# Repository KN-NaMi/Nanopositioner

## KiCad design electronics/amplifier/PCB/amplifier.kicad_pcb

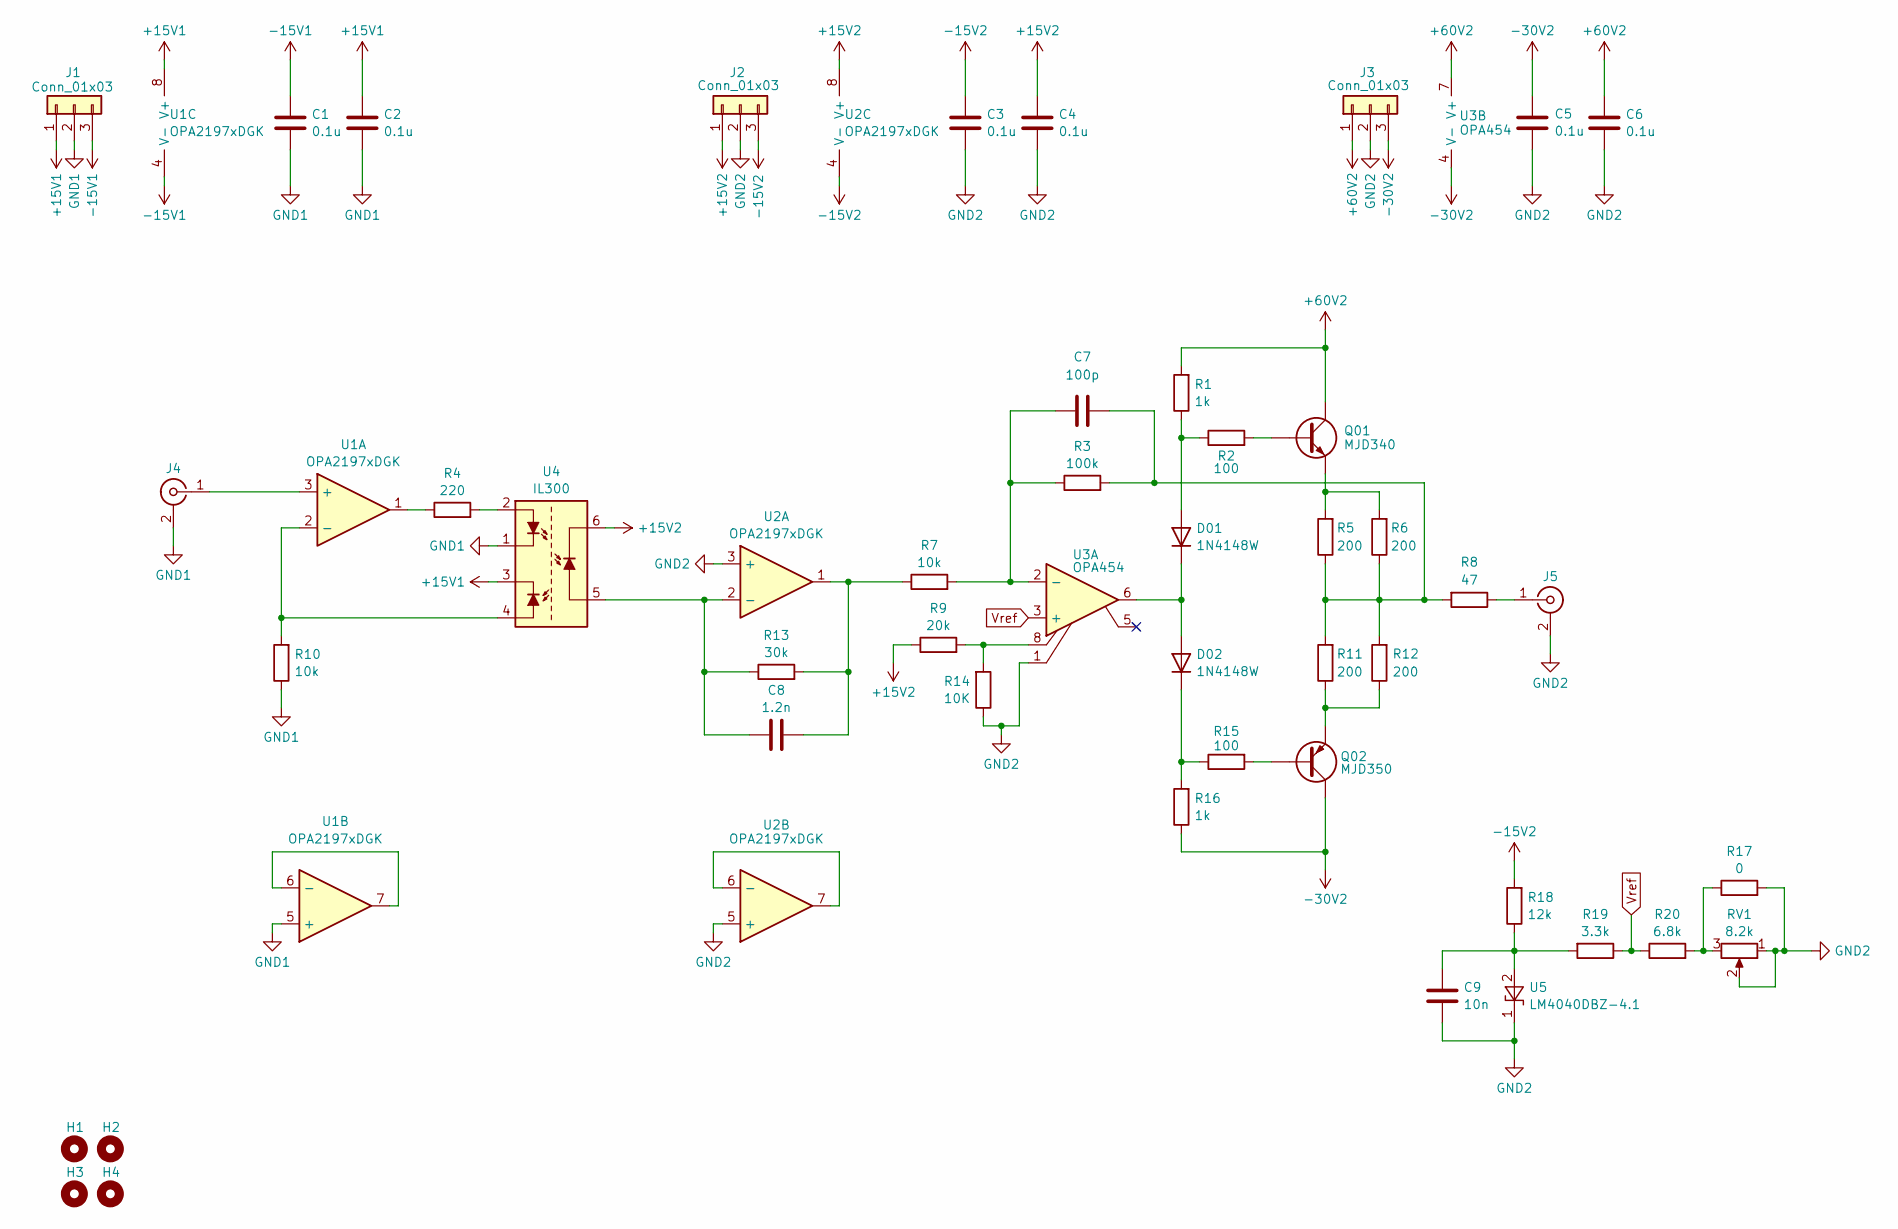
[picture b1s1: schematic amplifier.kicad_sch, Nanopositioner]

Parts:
C1, C2, C3, C4, C5: 0.1u; R_0603_1608Metric; Digikey 399-C0603C104K5RACTUCT-ND
C6: 0.1u; R_0603_1608Metric; Digikey 490-3285-1-ND
C7: 100p; C_0603_1608Metric; Digikey 3372-0603B101K101SDTR-ND
C8: 1.2n; C_0603_1608Metric; Digikey 490-1453-1-ND
C9: 10n; C_0603_1608Metric; Digikey 399-C0603C103K5RACTUCT-ND
D01, D02: 1N4148W; D_SOD-123; Digikey 1655-1N4148WCT-ND
H1, H2, H3, H4: MountingHole; MountingHole_3.2mm_M3_DIN965
J1, J2, J3: Conn_01x03; TerminalBlock_Phoenix_PT-1,5-3-5.0-H_1x03_P5.00mm_Horizontal; Digikey 732-10956-ND
J4, J5: Conn_Coaxial; SMA_Amphenol_132134_Vertical; Digikey 2073-RFPC-SMA28-F-ND
Q01: MJD340; TO-252-3_TabPin4; Digikey MJD340T4GOSCT-ND
Q02: MJD350; TO-252-3_TabPin4; Digikey MJD350T4GOSCT-ND
R1, R16: 1k; R_0603_1608Metric; Digikey 541-2788-1-ND
R2, R15: 100; R_0603_1608Metric; Digikey 541-2786-1-ND
R3: 100k; R_0805_2012Metric; Digikey 541-2850-1-ND
R4: 220; R_0603_1608Metric; Digikey 541-10437-1-ND
R5, R6, R11, R12: 200; R_2512_6332Metric; Digikey A116015CT-ND
R7, R10: 10k; R_0603_1608Metric; Digikey 541-2795-1-ND
R8: 47; R_2512_6332Metric; Digikey 118-CHP2512AFX-47R0ELFCT-ND
R9: 20k; R_0603_1608Metric; Digikey 541-2797-1-ND
R13: 30k; R_0603_1608Metric; Digikey 541-10453-1-ND
R14: 10K; R_0603_1608Metric; Digikey 541-2795-1-ND
R17: 0; R_0603_1608Metric
R18: 12k; R_0603_1608Metric; Digikey 541-10428-1-ND
R19: 3.3k; R_0603_1608Metric; Digikey 541-10464-1-ND
R20: 6.8k; R_0603_1608Metric; Digikey 541-10489-1-ND
RV1: 8.2k; Potentiometer_Vishay_T93YA_Vertical; Digikey 716-T63YA802KT20-ND
U1, U2: OPA2197xDGK; VSSOP-8_3x3mm_P0.65mm; Digikey 296-47349-1-ND
U3: OPA454; DDA0008J; Digikey 296-41370-1-ND
U4: IL300; SMDIP-8_W9.53mm_Clearance8mm; Digikey IL300-DEFG-X007-ND
U5: LM4040DBZ-4.1; SOT-23; Digikey LM4040AIM3-4.1/NOPBCT-ND

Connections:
+15V1: C2.1, J1.1, U1.8 (V+), U4.3
+15V2: C4.1, J2.1, R9.1, U2.8 (V+), U4.6
+60V2: C6.1, J3.1, Q01.C, R1.2, U3.7 (V+)
-15V1: C1.1, J1.3, U1.4 (V-)
-15V2: C3.1, J2.3, R18.2, U2.4 (V-)
-30V2: C5.1, J3.3, Q02.C, R16.1, U3.4 (V-)
GND1: C1.2, C2.2, J1.2, J4.2 (Ext), R10.1, U1.5 (+), U4.1
GND2: C3.2, C4.2, C5.2, C6.2, C9.1, J2.2, J3.2, J5.2 (Ext), R14.1, R17.2, RV1.1, RV1.2, U2.3 (+), U2.5 (+), U3.1, U5.1 (K)
unnamed: C7.2, R3.2, R5.1, R6.1, R8.2, R11.2, R12.2
unnamed: C8.2, R7.1, R13.2, U2.1
unnamed: D01.2 (A), R1.1, R2.1
unnamed: D01.1 (K), D02.2 (A), U3.6
unnamed: D02.1 (K), R15.1, R16.2
unnamed: J4.1 (In), U1.3 (+)
unnamed: J5.1 (In), R8.1
unnamed: Q01.B, R2.2
unnamed: Q01.E, R5.2, R6.2
unnamed: Q02.B, R15.2
unnamed: Q02.E, R11.1, R12.1
unnamed: R4.1, U1.1
unnamed: R4.2, U4.2
unnamed: R9.2, R14.2, U3.8
unnamed: R17.1, R20.2, RV1.3
unnamed: R10.2, U1.2 (-), U4.4
unnamed: U1.6 (-), U1.7
unnamed: C8.1, R13.1, U2.2 (-), U4.5
unnamed: U2.6 (-), U2.7
unnamed: C7.1, R3.1, R7.2, U3.2 (-)
unnamed: C9.2, R18.1, R19.2, U5.2 (A)
Vref: R19.1, R20.1, U3.3 (+)

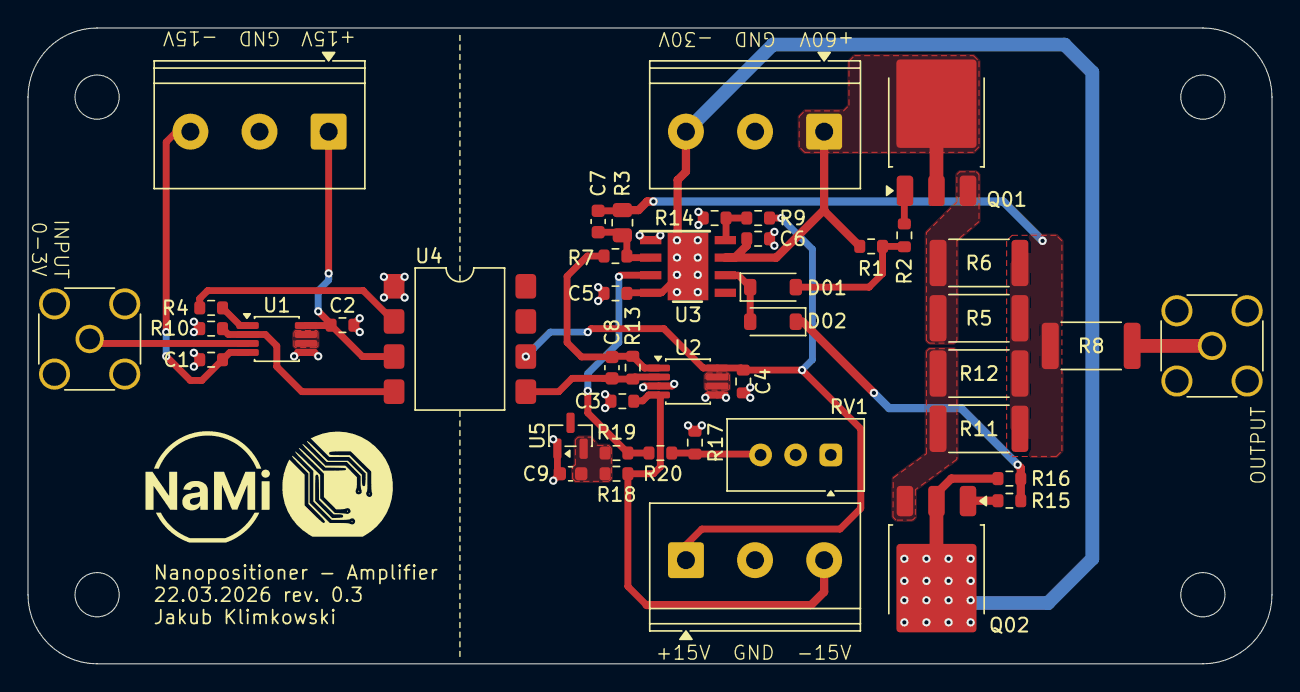
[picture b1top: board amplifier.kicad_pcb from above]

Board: 2 copper layers, 90.0 x 46.0 mm, 48 parts (0 on the bottom side), 30 nets.

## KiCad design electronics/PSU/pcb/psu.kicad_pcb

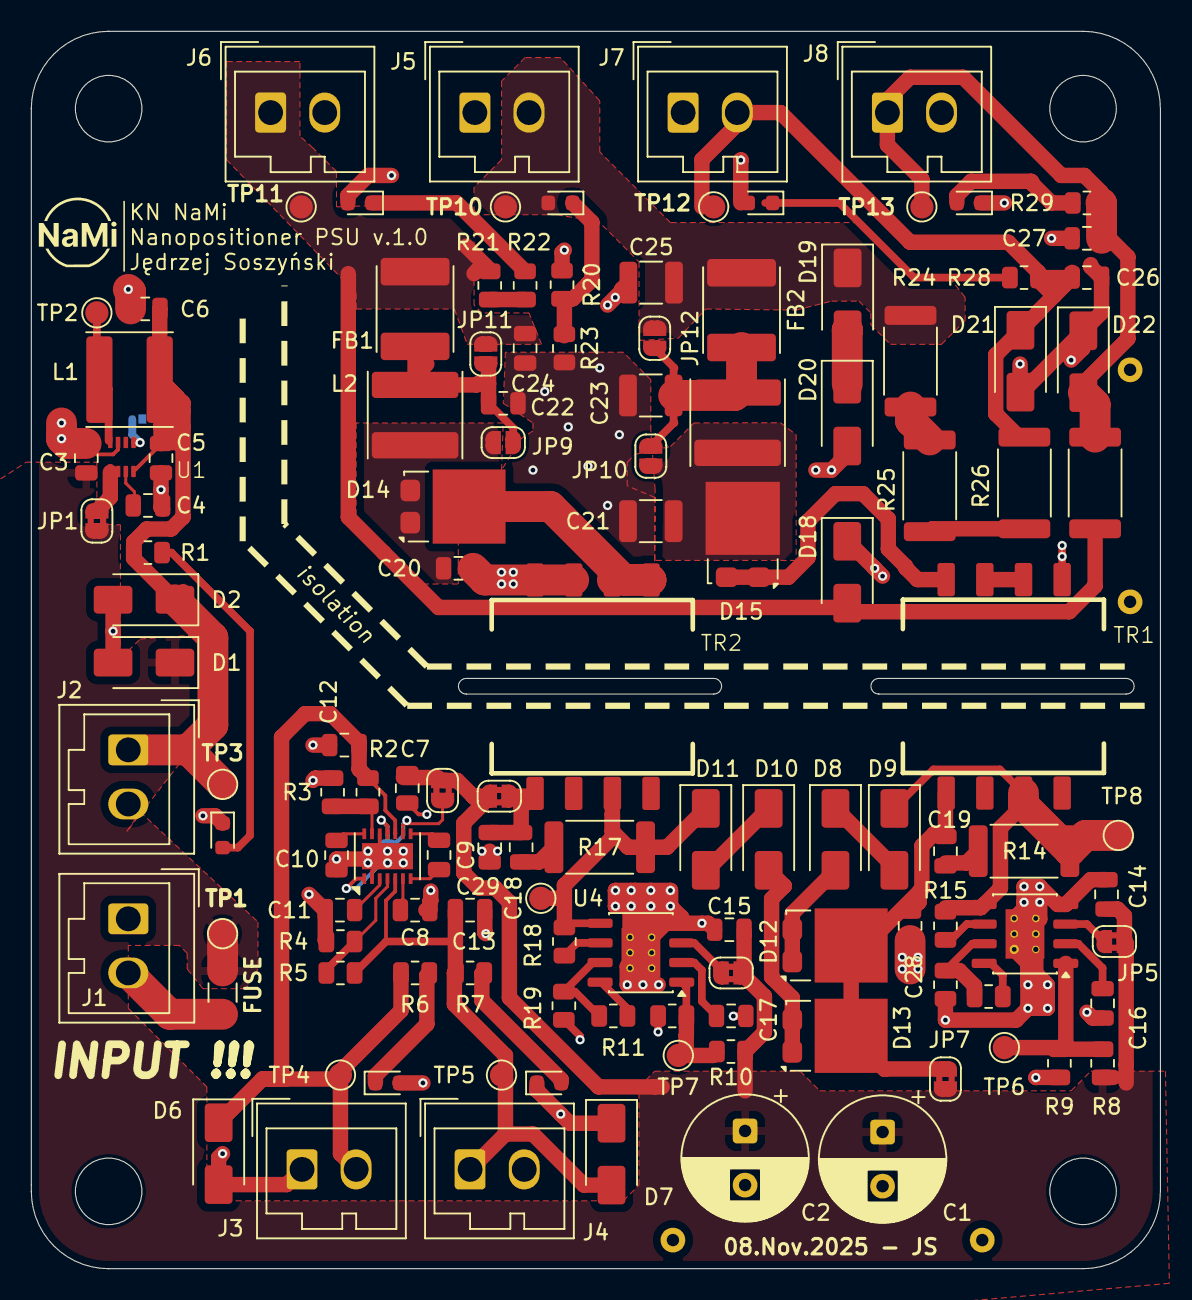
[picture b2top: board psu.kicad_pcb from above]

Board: 2 copper layers, 73.0 x 80.0 mm, 132 parts (1 on the bottom side), 63 nets.

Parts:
C1, C2: 220u; CP_Radial_D8.0mm_P3.50mm
C3, C5, C6, C7, C8, C12, C13, C14, C15, C20, C22, C24, C28, C29: 10u; C_0805_2012Metric
C4, C9, C16, C17, C26, C27: 1u; C_0805_2012Metric
C10, C11: 10n; C_0805_2012Metric
C18, C19: 1n; C_0805_2012Metric
C21, C23, C25: 10u; C_1210_3225Metric
D1: Z1SMA27; D_SMA
D2: Z1SMA5.6; D_SMA
D3, D4, D5, D16, D17, D23, D24: LED; LED_0603_1608Metric
D6, D7: Z1SMA16; D_SMA
D8, D10, D18, D19, D20: Z1SMA39; D_SMA
D9, D11, D21, D22: Z1SMA15; D_SMA
D12, D13, D14, D15: V8PM10S; TO-277A
F1: SBF32252ASTP; Fuse_1206_3216Metric
FB1, FB2: SPB0705-R12M; L_Coilcraft_1515SQ-68N
H1, H2, H3, H4: MountingHole; MountingHole_4.3mm_M4_ISO14580
J1, J2, J3, J4, J5, J6, J7, J8: Conn_01x02_Socket; Wago_734-132_1x02_P3.50mm_Vertical
JP1, JP4, JP5, JP6, JP7, JP13: SolderJumper_2_Bridged; SolderJumper-2_P1.3mm_Bridged2Bar_RoundedPad1.0x1.5mm
JP2: SolderJumper_2_Open; SolderJumper-2_P1.3mm_Bridged_RoundedPad1.0x1.5mm
JP3: Jumper_2_Bridged; C_Axial_L12.0mm_D6.5mm_P20.00mm_Horizontal
JP8: Jumper_2_Bridged; C_Axial_L12.0mm_D6.5mm_P15.00mm_Horizontal
JP9, JP10, JP11, JP12: SolderJumper_2_Open; SolderJumper-2_P1.3mm_Open_RoundedPad1.0x1.5mm
L1, L2, L3: 68uH; L_Wuerth_MAPI-5030
R1: 500R; R_0805_2012Metric
R2, R5: 1.15M; R_0805_2012Metric
R3, R4: 100k; R_0805_2012Metric
R6, R7, R20, R21, R28, R29: 1k; R_0805_2012Metric
R8, R10: 680k; R_0805_2012Metric
R9, R11: 48k; R_0805_2012Metric
R12, R13: 115k; R_0805_2012Metric
R14, R17: 39R; R_2512_6332Metric
R15: 149k; R_0805_2012Metric
R16, R19, R22, R23: 10k; R_0805_2012Metric
R18: 150k; R_0805_2012Metric
R24, R25, R26, R27: 500R; R_2512_6332Metric
TP1, TP2, TP3, TP4, TP5, TP6, TP7, TP8, TP9, TP10, TP11, TP12, TP13: TestPoint; TestPoint_Pad_D1.5mm
TR1, TR2: 750313445
U1: ADPL16000B; ADPL16000footprint
U2: LTC3260xDE; DFN-14-1EP_3x4mm_P0.5mm_EP1.7x3.3mm
U3, U4: ADPL54203; SOIC-8-1EP_3.9x4.9mm_P1.27mm_EP2.514x3.2mm_ThermalVias

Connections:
+5V: C5.2, C6.2, D2.1 (K), J2.1, L1.2, R1.1, TP3.1, U1.4 (FB)
+15V_pri: C12.2, D6.1 (K), J3.2, R2.1, R6.1, TP4.1, U2.10 (LDO^{+})
+15V_sec: C26.1, D21.1 (K), J7.2, R26.2, R28.1, TP12.1
+24V: C1.1, C2.1, C3.1, C7.2, C14.2, C15.2, D1.1 (K), F1.2, JP1.1 (A), JP4.1 (A), JP5.2 (B), JP6.2 (B), JP7.2 (B), JP13.1 (A), R8.1, R10.1, TP1.1
+60V: C25.2, D17.2 (A), D19.1 (K), FB2.2, J5.2, JP12.1 (A), R24.1, TP10.1
-15V_pri: C13.1, D7.2 (A), J4.1, R5.2, R7.2, TP5.1, U2.5 (LDO^{-})
-15V_sec: C27.2, D22.2 (A), J8.1, R27.1, R29.2, TP13.1
-30V: C24.2, D18.2 (A), FB1.2, J6.1, JP11.2 (B), R21.2, R27.2, TP11.1
/5V/LED: D3.2 (A), R1.2
/5V/fuse: F1.1, J1.2
/+60V_-30V_sec/+L: C21.2, D15.3 (K), JP10.2 (B), L3.1
/+60V_-30V_sec/-L: C20.1, D14.1 (A), D14.2 (A), JP9.1 (A), L2.2
/+60V_-30V_sec/EN: R8.2, R9.2, TP6.1, U3.1 (EN)
/+60V_-30V_sec/EN': R10.2, R11.2, TP7.1, U4.1 (EN)
/+60V_-30V_sec/INTVcc: C16.1, U3.2 (INTVcc)
/+60V_-30V_sec/INTVcc': C17.1, U4.2 (INTVcc)
/+60V_-30V_sec/RFB: R15.2, U3.6 (RFB)
/+60V_-30V_sec/RFB': R18.2, U4.6 (RFB)
/+60V_-30V_sec/Rref: R12.1, R16.1, U3.7 (Rref)
/+60V_-30V_sec/Rref': R13.1, R19.1, U4.7 (Rref)
/+60V_-30V_sec/SW: D9.1 (K), R14.2, R15.1, TP8.1, TR1.2, U3.5 (SW)
/+60V_-30V_sec/SW': D11.1 (K), R17.2, R18.1, TP9.1, TR2.2, U4.5 (SW)
/+60V_-30V_sec/Snub: C19.1, R14.1
/+60V_-30V_sec/Snub': C18.1, R17.1
/+60V_-30V_sec/power: C19.2, C28.1, D12.3 (K), D13.3 (K), JP7.1 (A), TR1.4
/+60V_-30V_sec/sec1: D15.1 (A), D15.2 (A), TR1.5
/+60V_-30V_sec/sec2: D14.3 (K), TR2.7, TR2.8
/+-15V_pri/ADJ+: R2.2, R3.1, U2.13 (ADJ^{+})
/+-15V_pri/ADJ-: R4.2, R5.1, U2.4 (ADJ^{-})
/+-15V_pri/BYP+: C10.1, U2.14 (BYP^{+})
/+-15V_pri/BYP-: C11.2, U2.3 (BYP^{-})
/+-15V_pri/C+: C9.1, U2.8 (C^{+})
/+-15V_pri/C-: C9.2, U2.7 (C^{-})
GND: C1.2, C2.2, C3.2, C4.2, C5.1, C6.1, C7.1, C8.2, C10.2, C11.1, C12.1, C13.2, C14.1, C15.1, C16.2, C17.2, C28.2, C29.2, D1.2 (A), D2.2 (A), D3.1 (K), D4.2 (A), D5.1 (K), D6.2 (A), D7.1 (K), J1.1, J2.2, J3.1, J4.2, JP2.1 (A), JP3.1 (A), JP3.2 (B), R3.2, R4.1, R9.1, R11.1, R16.2, R19.2, U1.7 (GND), U2.2 (RT), U2.12 (MODE), U2.15 (GND), U3.3 (Vin), U3.4 (GND), U3.9 (GND(pad)), U4.4 (GND), U4.9 (GND(pad))
GNDs: C20.2, C21.1, C22.2, C23.1, C24.1, C25.1, C26.2, C27.1, D16.2 (A), D18.1 (K), D20.2 (A), D21.2 (A), D22.1 (K), D23.2 (A), D24.1 (K), J5.1, J6.2, J7.1, J8.2, JP8.1 (A), JP8.2 (B), R22.2, R23.2, TR1.8, TR2.5, TR2.6
unnamed: D4.1 (K), R6.2
unnamed: D5.2 (A), R7.1
unnamed: D8.2 (A), D12.1 (A), D12.2 (A)
unnamed: D8.1 (K), D9.2 (A)
unnamed: D10.2 (A), D13.1 (A), D13.2 (A)
unnamed: D10.1 (K), D11.2 (A)
unnamed: D16.1 (K), R20.1
unnamed: D17.1 (K), R22.1, R23.1
unnamed: D19.2 (A), D20.1 (K)
unnamed: D23.1 (K), R28.2
unnamed: D24.2 (A), R29.1
unnamed: JP1.2 (B), U1.1 (Vin), U1.2 (EN)
unnamed: JP2.2 (B), U1.5 (MODE)
unnamed: JP4.2 (B), U2.1 (EN^{+}), U2.9 (V_{IN}), U2.11 (EN^{-})
unnamed: JP5.1 (A), U3.3 (Vin)
unnamed: JP6.1 (A), U4.3 (Vin)
unnamed: C23.2, FB2.1, JP10.1 (A), JP12.2 (B), L3.2
unnamed: C22.1, FB1.1, JP9.2 (B), JP11.1 (A), L2.1
unnamed: C18.2, C29.1, JP13.2 (B), TR2.4
unnamed: R20.2, R21.1
unnamed: R24.2, R25.1
unnamed: R25.2, R26.1
unnamed: TR1.6, TR1.7
unnamed: L1.1, TP2.1, U1.8 (LX)
unnamed: C4.1, U1.3 (Vcc)
unnamed: C8.1, U2.6 (V_{OUT})
unnamed: R12.2, U3.8 (Tc)
unnamed: R13.2, U4.8 (Tc)

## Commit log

2025-05-25 add amplifier sch
2025-05-27 change to inverting opamp configuration
2025-10-20 Add software and basic documentation
2025-10-21 Rename folders
2025-10-26 Schemat PSU + symulacje PSU
2025-10-27 poprawki do schematu psu
2025-11-09 added PSU PCB design files
2025-11-12 final changes
2025-11-17 restructured repo according to the template
2025-11-17 Refactor repo
2025-11-23 update pcb signature
2026-03-23 feat: amplifier board rev. 03
